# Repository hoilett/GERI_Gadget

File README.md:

# GERI_Gadget (under development so bookmark this page and stay tuned!)

The GERI Gadget is a small smartwatch I made for students taking my Biomedical Instrumentation class during GERI Summer Residential 2018. GERI stands for Gifted Education Resource Institute and it's a wonderful group at Purdue that specializes on educational policy, training, teaching methods, etc. of gifted students in K-12. Check out all their wonderful work on their website: [Purdue GERI](https://www.education.purdue.edu/geri/)

Anyways, I wanted to create a device that allowed students to get hands-on experience building some sort of Biomedical device. This meant adding enough peripherals so that students could make anything from a pedometer to even a fall alert. Revision A of the watch contains a few peripherals, namely:
* ATSAMD21 Microcontroller
* On/Off Switch
* Battery Charging Circuit
* OLED
* Two pushbuttons
* Buzzer
* Photoresistor
* LED
* LIS3DH Accelerometer

_**This section is still under development. I will be filling it out over the next few weeks so bookmark this page and stay tuned!**_

## Programming the Microcontroller
###### **A. Installing the board definitions for SparkFun's SAMD21 Dev Breakout Board**
###### **B. Installing the proper code libraries**
You will need three libraries to get started with the GERI Gadget:
1. Adafruit's SSD1306 Library
2. Adafruit's GFX Library
3. SparkFun's LIS3DH Accelerometer Library

## Advanced Setup Instructions
## 1. Assembling the printed circuit board
## 2. Booloading the ATSAMD21

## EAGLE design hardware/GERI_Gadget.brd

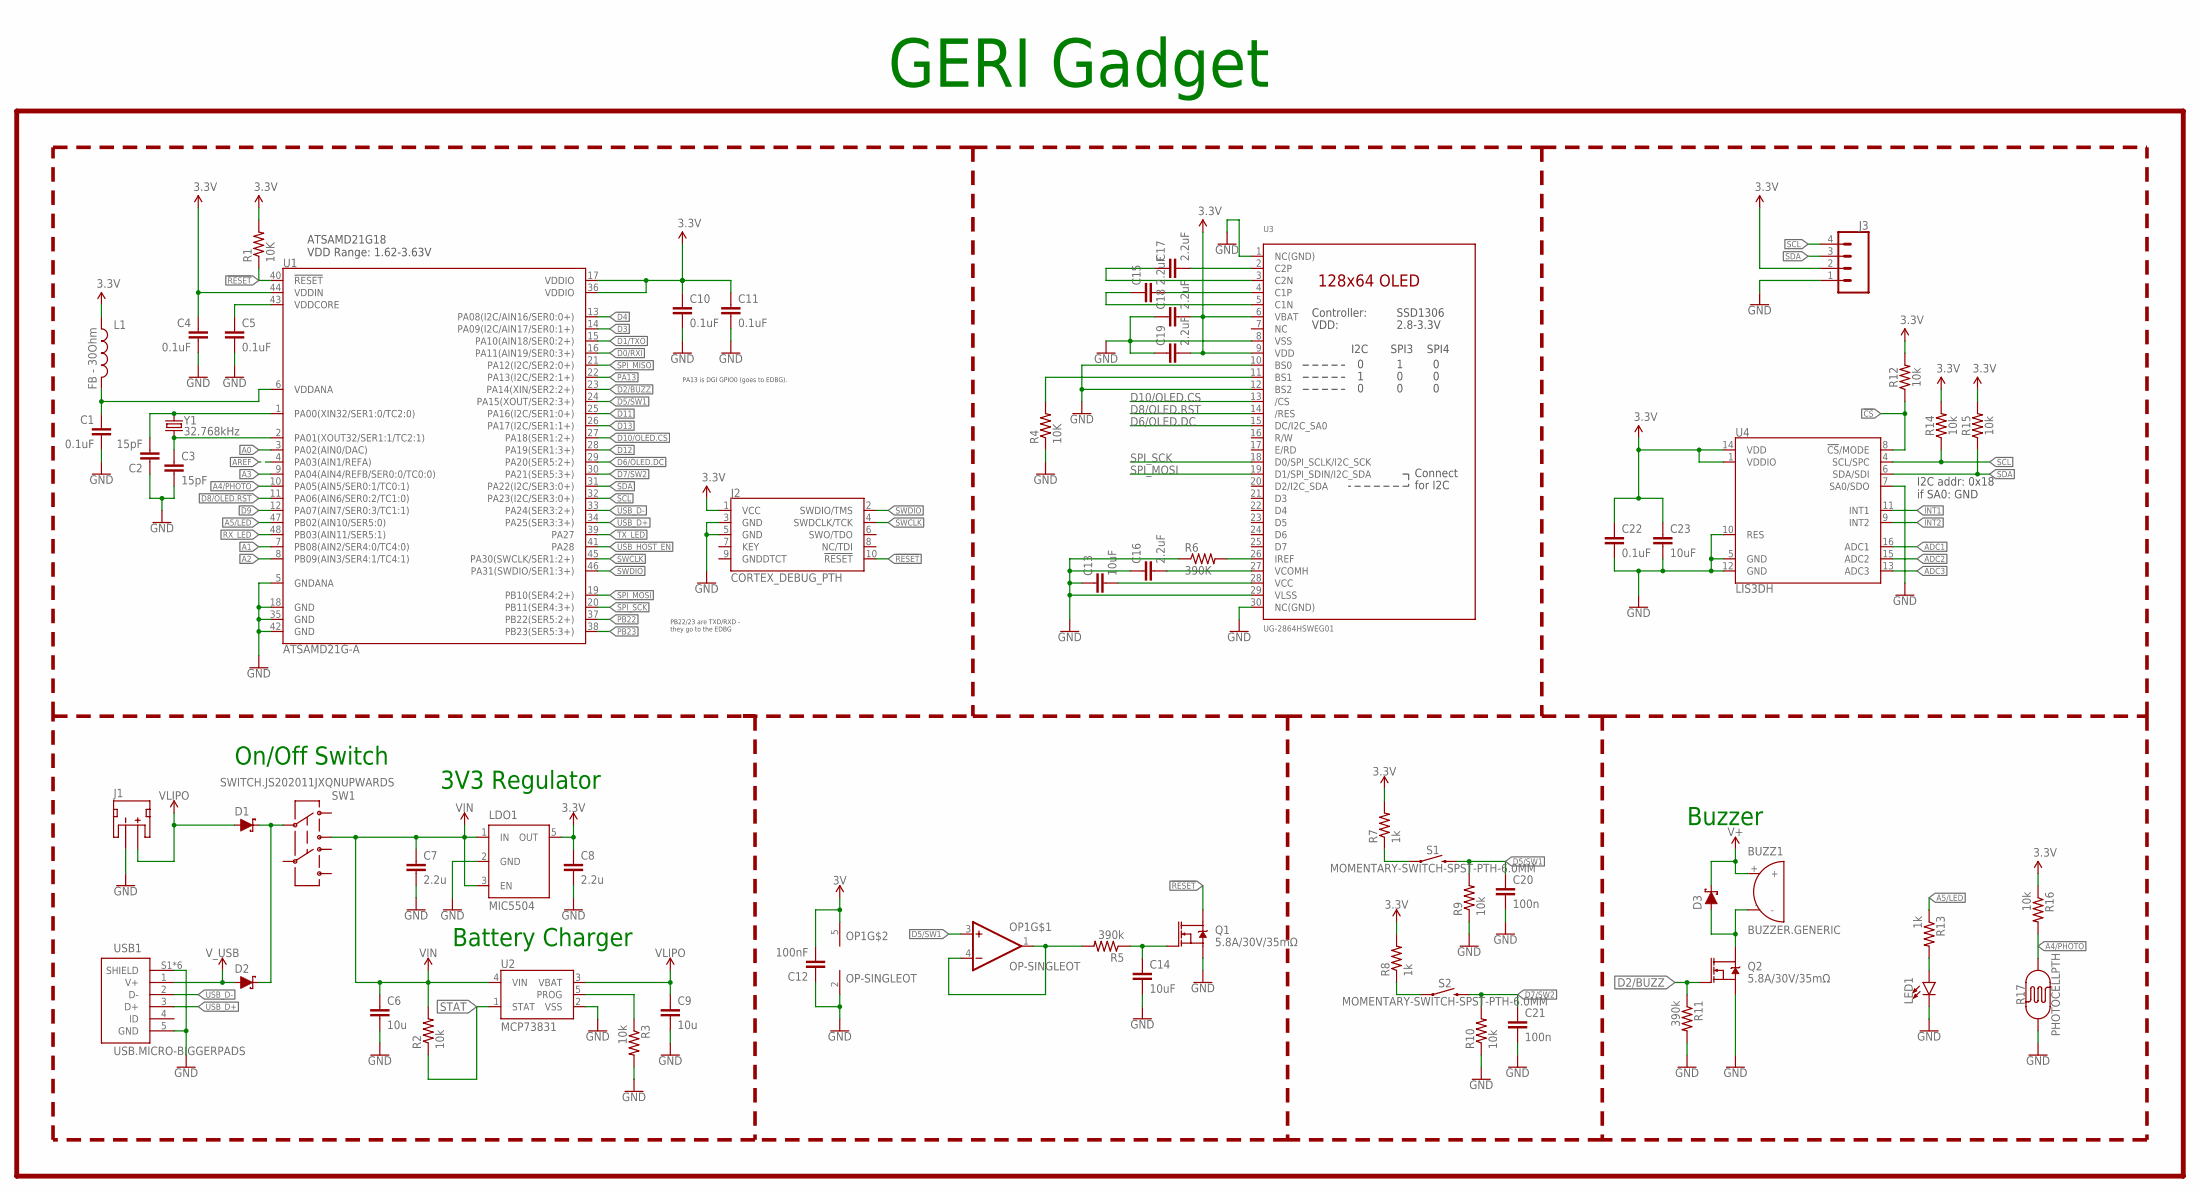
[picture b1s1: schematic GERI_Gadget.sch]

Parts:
BUZZ1: BUZZER.GENERIC; PIEZO-1
C1, C4, C5, C10, C11: 0.1uF; C0402
C2, C3: 15pF; C0402
C6, C9: 10u; C0603
C7, C8: 2.2u; C0603
C12: 100nF; C0402
C13, C14: 10uF; C0603
C15, C16, C17, C18, C19: 2.2uF; C0603
C20, C21: 100n; C0402
C22: 0.1uF; 0402
C23: 10uF; 0603
D1, D2, D3: SCHOTTKY-USC; USC
J1: JST_2MM_MALE; JST-2-SMD
J2: CORTEX_DEBUG_PTH; 2X5-PTH-1.27MM
J3: CONN_04; 1X04
L1: FB - 30Ohm; 0603
LDO1: MIC5504; SOT23-5
LED1: LED5MM; LED_5MM
OP1: OP-SINGLEOT; SOT23-5
Q1, Q2: 5.8A/30V/35mΩ; SOT23-3
R1, R4: 10K; R0402-BIGGER
R2, R3, R9, R10, R16: 10k; R0402-BIGGER
R5, R11: 390k; R0402-BIGGER
R6: 390K; R0402-BIGGER
R7, R8, R13: 1k; R0402-BIGGER
R12, R14, R15: 10k; 0402
R17: PHOTOCELLPTH; PHOTOCELL
REV1: REVISION.A; REV.A
S1, S2: MOMENTARY-SWITCH-SPST-PTH-6.0MM; TACTILE_SWITCH_PTH_6.0MM
SW1: SWITCH.JS202011JXQNUPWARDS; SWITCH.00
U1: ATSAMD21G-A; TQFP-48
U2: MCP73831; SOT23-5
U3: UG-2864HSWEG01; UG-2864HSWEG01_0.96IN_NO-WRAPAROUND
U4: LIS3DH; LGA-16-3X3
USB1: USB.MICRO-BIGGERPADS; USB-MICRO-01.BIGGERPADS
Y1: 32.768kHz; CRYSTAL-SMD-3.2X1.5MM

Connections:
3.3V: C4.1, C8.1, C10.1, C11.1, C18.2, C19.2, C22.1, C23.1, J2.1 (VCC), J3.2, L1.1, LDO1.5 (OUT), R1.2, R7.2, R8.2, R12.2, R14.2, R15.2, R16.1, U1.17 (VDDIO), U1.36 (VDDIO), U1.44 (VDDIN), U3.6 (VBAT), U3.9 (VDD), U4.1 (VDDIO), U4.14 (VDD)
3V: C12.2, OP1.5 (V+)
!CS: R12.1, U4.8 (!CS!/MODE)
!RESET: J2.10 (!RESET), Q1.3 (D), R1.1, U1.40 (!RESET!)
A0: U1.3 (PA02(AIN0/DAC))
A1: U1.7 (PB08(AIN2/SER4:0/TC4:0))
A2: U1.8 (PB09(AIN3/SER4:1/TC4:1))
A3: U1.9 (PA04(AIN4/REFB/SER0:0/TC0:0))
A4/PHOTO: R16.2, R17.2, U1.10 (PA05(AIN5/SER0:1/TC0:1))
A5/LED: R13.1, U1.47 (PB02(AIN10/SER5:0))
ADC1: U4.16 (ADC1)
ADC2: U4.15 (ADC2)
ADC3: U4.13 (ADC3)
AREF: U1.4 (PA03(AIN1/REFA))
D0/RXI: U1.16 (PA11(AIN19/SER0:3+))
D1/TXO: U1.15 (PA10(AIN18/SER0:2+))
D2/BUZZ: Q2.1 (G), R11.1, U1.23 (PA14(XIN/SER2:2+))
D3: U1.14 (PA09(I2C/AIN17/SER0:1+))
D4: U1.13 (PA08(I2C/AIN16/SER0:0+))
D5/SW1: C20.1, OP1.3 (+IN), R9.2, S1.3 (2), U1.24 (PA15(XOUT/SER2:3+))
D6/OLED.DC: U1.29 (PA20(SER5:2+)), U3.15 (DC/I2C_SA0)
D7/SW2: C21.1, R10.2, S2.3 (2), U1.30 (PA21(SER5:3+))
D8/OLED.RST: U1.11 (PA06(AIN6/SER0:2/TC1:0)), U3.14 (/RES)
D9: U1.12 (PA07(AIN7/SER0:3/TC1:1))
D10/OLED.CS: U1.27 (PA18(SER1:2+)), U3.13 (/CS)
D11: U1.25 (PA16(I2C/SER1:0+))
D12: U1.28 (PA19(SER1:3+))
D13: U1.26 (PA17(I2C/SER1:1+))
GND: C1.2, C2.1, C3.2, C4.2, C5.2, C6.2, C7.2, C8.2, C9.2, C10.2, C11.2, C12.1, C13.1, C14.2, C16.1, C18.1, C19.1, C20.2, C21.2, C22.2, C23.2, J1.1 (-), J2.3 (GND), J2.5 (GND), J3.1, LDO1.2 (GND), LED1.K (C), OP1.2 (V-), Q1.2 (S), Q2.2 (S), R3.2, R4.1, R6.1, R9.1, R10.1, R11.2, R17.1, U1.5 (GNDANA), U1.18 (GND), U1.35 (GND), U1.42 (GND), U2.2 (VSS), U3.1 (NC(GND)), U3.8 (VSS), U3.10 (BS0), U3.12 (BS2), U3.29 (VLSS), U3.30 (NC(GND)), U4.5 (GND), U4.7 (SA0/SDO), U4.10 (RES), U4.12 (GND), USB1.5 (GND), USB1.S1 (SHIELD), USB1.S2 (SHIELD), USB1.S3 (SHIELD), USB1.S4 (SHIELD), USB1.S5 (SHIELD), USB1.S6 (SHIELD)
INT1: U4.11 (INT1)
INT2: U4.9 (INT2)
unnamed: C2.2, U1.1 (PA00(XIN32/SER1:0/TC2:0)), Y1.P$2 (2)
unnamed: LED1.A, R13.2
unnamed: C3.1, U1.2 (PA01(XOUT32/SER1:1/TC2:1)), Y1.P$1 (1)
unnamed: OP1.1 (OUT), OP1.4 (-IN), R5.2
unnamed: R7.1, S1.1
unnamed: R8.1, S2.1
unnamed: R3.1, U2.5 (PROG)
unnamed: D1.- (C), D2.- (C), SW1.2
unnamed: C14.1, Q1.1 (G), R5.1
unnamed: R4.2, U3.11 (BS1)
unnamed: BUZZ1.-, D3.+ (A), Q2.3 (D)
unnamed: R6.2, U3.26 (IREF)
unnamed: C17.2, U3.2 (C2P)
unnamed: C17.1, U3.3 (C2N)
unnamed: C15.2, U3.4 (C1P)
unnamed: C15.1, U3.5 (C1N)
unnamed: C13.2, U3.28 (VCC)
unnamed: C16.2, U3.27 (VCOMH)
PA13: U1.22 (PA13(I2C/SER2:1+))
PB22: U1.37 (PB22(SER5:2+))
PB23: U1.38 (PB23(SER5:3+))
RX_LED: U1.48 (PB03(AIN11/SER5:1))
SCL: J3.4, R14.1, U1.32 (PA23(I2C/SER3:0+)), U4.4 (SCL/SPC)
SDA: J3.3, R15.1, U1.31 (PA22(I2C/SER3:0+)), U4.6 (SDA/SDI)
SPI_MISO: U1.21 (PA12(I2C/SER2:0+))
SPI_MOSI: U1.19 (PB10(SER4:2+)), U3.19 (D1/SPI_SDIN/I2C_SDA)
SPI_SCK: U1.20 (PB11(SER4:3+)), U3.18 (D0/SPI_SCLK/I2C_SCK)
STAT: R2.1, U2.1 (STAT)
SWCLK: J2.4 (SWDCLK/TCK), U1.45 (PA30(SWCLK/SER1:2+))
SWDIO: J2.2 (SWDIO/TMS), U1.46 (PA31(SWDIO/SER1:3+))
TX_LED: U1.39 (PA27)
USB_D+: U1.34 (PA25(SER3:3+)), USB1.3 (D+)
USB_D-: U1.33 (PA24(SER3:2+)), USB1.2 (D-)
USB_HOST_EN: U1.41 (PA28)
V+: BUZZ1.+, D3.- (C)
VDDANA: C1.1, L1.2, U1.6 (VDDANA)
VDDCORE: C5.1, U1.43 (VDDCORE)
VIN: C6.1, C7.1, LDO1.1 (IN), LDO1.3 (EN), R2.2, SW1.3, U2.4 (VIN)
VLIPO: C9.1, D1.+ (A), J1.2 (+), U2.3 (VBAT)
V_USB: D2.+ (A), USB1.1 (V+)

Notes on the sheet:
PB22/23 are TXD/RXD - they go to the EDBG
PA13 is DGI GPIO0 (goes to EDBG).
ATSAMD21G18 VDD Range: 1.62-3.63V
3V3 Regulator
On/Off Switch
Battery Charger
Buzzer
I2C addr: 0x18 if SA0: GND
GERI Gadget

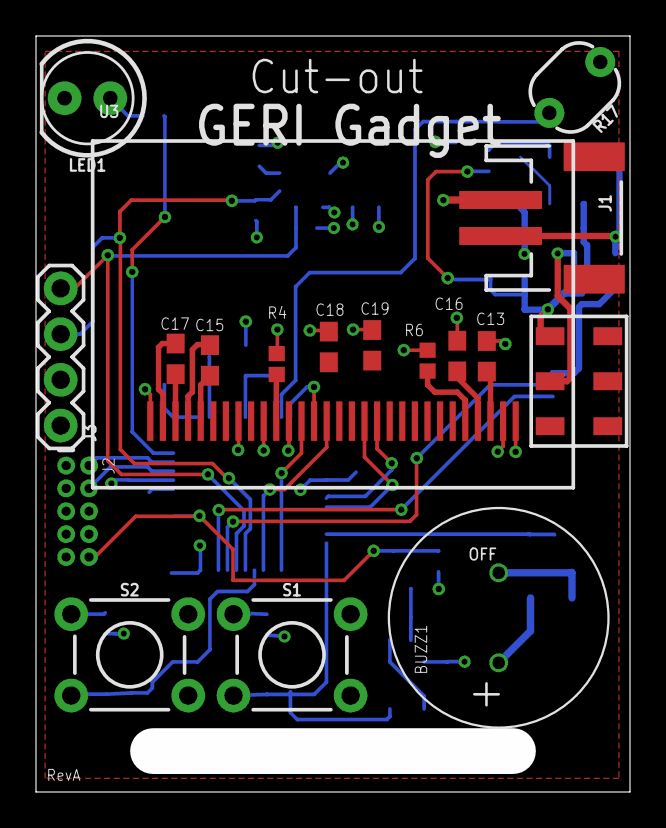
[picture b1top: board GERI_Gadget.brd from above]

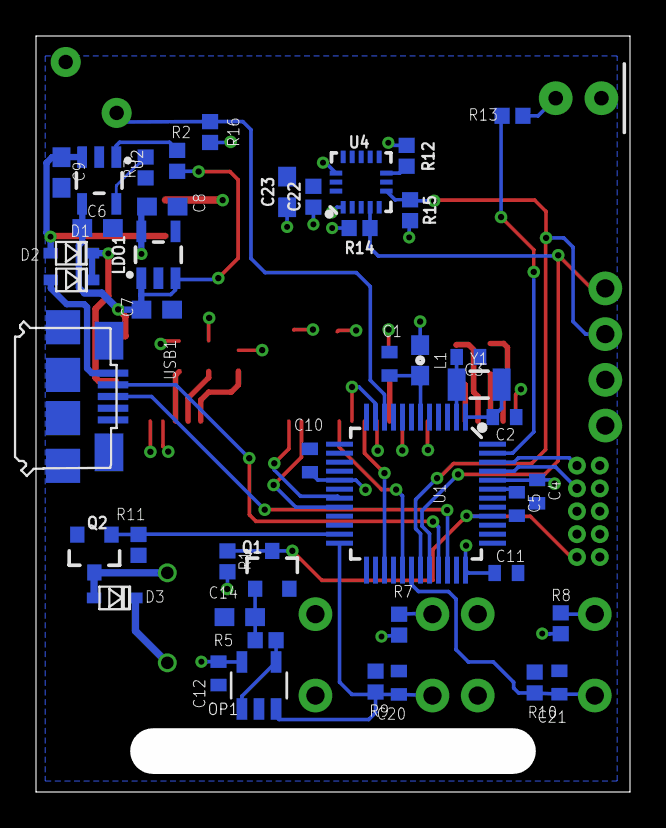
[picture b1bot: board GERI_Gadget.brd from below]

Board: 2 copper layers, 33.0 x 42.0 mm, 63 parts (44 on the bottom side), 46 nets.

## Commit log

2018-06-30 still working on these
2018-07-01 updates...almost done
2018-07-12 added changing screens example
2018-07-12 basic example of pedometer on watch
2018-07-12 simple exmpale
2018-07-12 initial try
2018-07-13 fixed issues with taking an extra button push to switch screens
2018-07-13 stopwatch
2018-07-13 fixed issues
2018-08-03 starting to add some images
2018-08-03 added smaller image
2018-08-03 added another smaller image

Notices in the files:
parts and their libraries:
SparkFun-Passives: Licensing: Creative Commons ShareAlike 4.0 International - https://creativecommons.org/licenses/by-sa/4.0
